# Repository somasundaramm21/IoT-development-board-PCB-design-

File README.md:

# IoT-development-board-PCB-design-
PCB Design and Kicad files for IoT development board

# 🔧 ESP32-C3 IoT Development Board – Designed with KiCad 8

This repository showcases the complete design journey of a **medium-complexity, four-layer IoT development board**, created using **KiCad 8**. The board features the **ESP32-C3** microcontroller along with built-in **environmental sensors**, **flash memory**, **microSD card support**, and a robust **power management system**—making it a powerful and flexible platform for modern IoT applications.

Unlike previous KiCad projects where I only explored new features, this time I set out to **test KiCad 8 in a real-world design workflow**—from schematic to layout, all the way to manufacturing and hardware validation. The result is this versatile, fully functional development board, designed, tested, and optimized using KiCad 8's latest capabilities.

---

## ✨ Key Features

- ✅ Real-world hardware tested with iterative debugging
- 🛠️ Designed entirely in **KiCad 8**
- ⚡️ Powered by **ESP32-C3** (RISC-V + Wi-Fi + BLE)
- 🔋 Battery and USB-C powered with onboard charging circuit
- 📦 Includes **SPI flash** and **microSD card** for flexible data storage
- 🌡️ Built-in sensors for real-time environmental monitoring
- 🧠 Expandable with AI/LLM capabilities using OpenAI-ESP32

---

## 📐 Tech Specs

### 🧠 Core Components

- **Microcontroller**: ESP32-C3 (RISC-V, Wi-Fi 4, Bluetooth Low Energy)
- **Power Input**: USB-C (for power and data) or LiPo battery (via JST)
- **Power Management**:
  - Dedicated LiPo charging circuit
  - Onboard 3.3V and 5V voltage regulators
- **Storage**:
  - MicroSD card slot for local logging
  - External SPI Flash for config/firmware/data

### 🌡️ Sensors & Inputs

- **BME280**: Temperature, humidity, and pressure
- **Ambient Light Sensor**
- **Microphone with Pre-Amplifier**: Sound monitoring and audio input

### 🔌 Interfaces

- **Protocols**: I2C, SPI
- **USB-to-UART Bridge**: For easy programming and serial debugging
- **GPIO Header**: Expandable for external devices/sensors
- **Test Points**: Available for hardware probing and diagnostics

### 🎛️ User Interaction

- **Buttons**: Boot and Reset
- **Indicators**: Status LEDs for power, charge, and operation
- **Form Factor**:
  - 4-layer PCB (signal, power, and ground planes)
  - Compact and EMI-conscious layout
  - Designed for manufacturability and hand-assembly

---

## 🌍 Applications

This board is a multipurpose platform designed for both prototyping and deployment in:

### 📊 Environmental Monitoring
Use the BME280 and light sensor to build smart weather stations, monitor air quality, or automate greenhouse conditions.

### 🧪 Data Logging
With both SPI flash and SD card, this board is perfect for remote or mobile data logging applications like field research or industrial monitoring.

### 🔋 Battery-Powered IoT Devices
Efficient power management and LiPo support allow you to create portable IoT nodes, wearables, or smart agriculture tools.

### 🔊 Audio-Responsive Systems
Use the microphone + preamp setup for audio monitoring, voice triggers, or sound-based analytics.

---

## 🤖 AI Integration with OpenAI-ESP32

This board is not just for sensors and data—it's also designed for **edge AI experiments**.

With the **OpenAI-ESP32 Arduino library** provided by Espressif, your IoT board can now:

- 🔈 **Understand Voice Commands**  
  Use the onboard microphone to build a smart home assistant that reacts to your natural language.

- 📈 **Analyze Sensor Trends**  
  Combine sensor data with OpenAI’s LLMs to generate meaningful summaries, alerts, or insights.

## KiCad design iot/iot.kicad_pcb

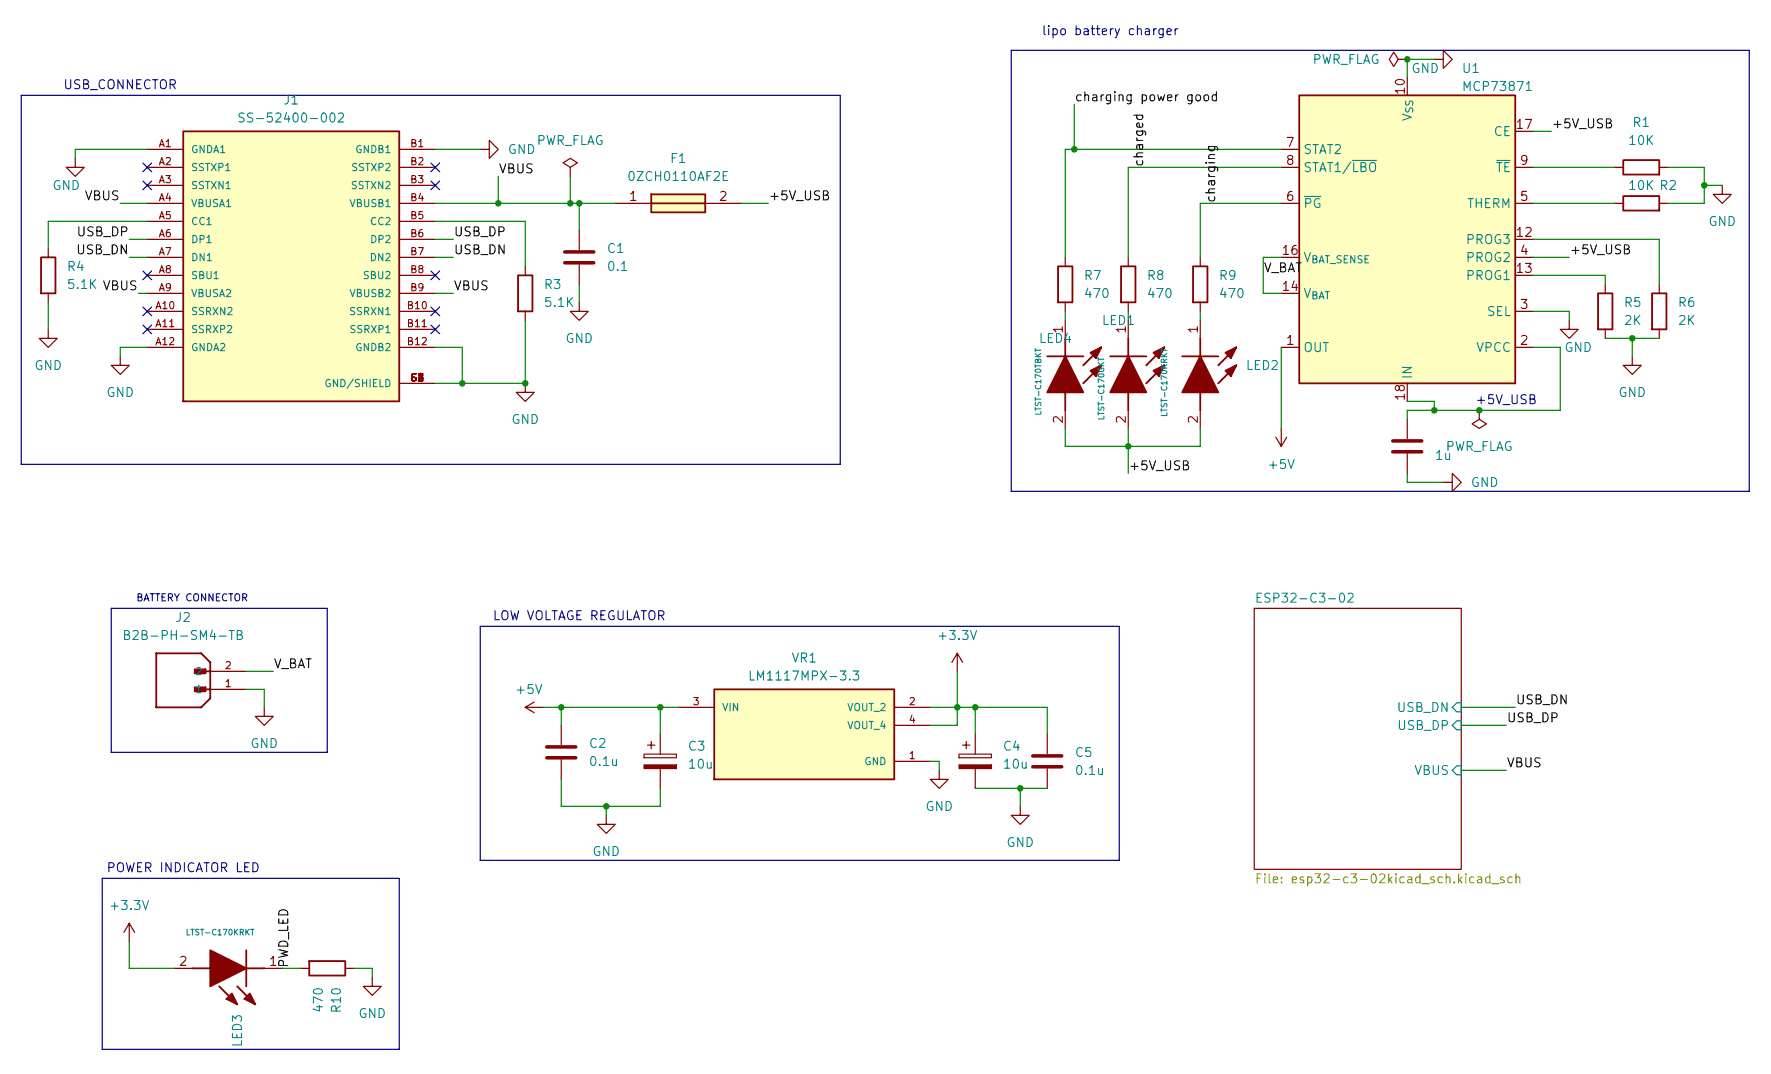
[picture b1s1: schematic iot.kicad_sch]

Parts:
C1: 0.1; C_0805_2012Metric
C2, C5: 0.1u; C_0805_2012Metric
C3, C4: 10u; RESC3216X125N
C6: 1u; C_0805_2012Metric
F1: 0ZCH0110AF2E; FUSC3226X100N; Manufacturer_Part_Number 0ZCH0110AF2E
J1: SS-52400-002; BELFUSE_SS-52400-002; PARTREV A0
J2: B2B-PH-SM4-TB; JST_B2B-PH-SM4-TB; PARTREV N/A
LED1: LTST-C170GKT; LEDC2012X120N; Manufacturer_Part_Number LTST-C170GKT; Mouser Part Number 859-LTST-C170GKT
LED2, LED3: LTST-C170KRKT; LEDC2012X120N; Manufacturer_Part_Number LTST-C170KRKT; Mouser Part Number 859-LTST-C170KRKT
LED4: LTST-C170TBKT; LEDC2012X120N; Manufacturer_Part_Number LTST-C170TBKT; Mouser Part Number 859-LTST-C170TBKT
R1, R2: 10K; R_0805_2012Metric
R3, R4: 5.1K; R_0805_2012Metric
R5, R6: 2K; R_0805_2012Metric
R7, R8, R9, R10: 470; R_0805_2012Metric
U1: MCP73871; QFN-20-1EP_4x4mm_P0.5mm_EP2.5x2.5mm
VR1: LM1117MPX-3.3; VREG_LM1117MPX-3.3; PARTREV O

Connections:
+3.3V: C4.1, C5.1, LED3.2 (A), VR1.2 (VOUT_2), VR1.4 (VOUT_4); also elsewhere on the board
+5V: C2.1, C3.1, U1.1 (OUT), U1.20 (OUT), VR1.3 (VIN)
/PWD_LED: LED3.1 (K), R10.2
/USB_DN: J1.A7 (DN1), J1.B7 (DN2); also elsewhere on the board
/USB_DP: J1.A6 (DP1), J1.B6 (DP2); also elsewhere on the board
/VBUS: C1.1, F1.1, J1.A4 (VBUSA1), J1.A9 (VBUSA2), J1.B4 (VBUSB1), J1.B9 (VBUSB2); also elsewhere on the board
/V_BAT: J2.2, U1.14 (V_{BAT}), U1.15 (V_{BAT}), U1.16 (V_{BAT_SENSE})
/charged: R8.1, U1.8 (STAT1/~LBO)
/charging: R9.1, U1.6 (~PG)
/charging power good: R7.1, U1.7 (STAT2)
GND: C1.2, C2.2, C3.2, C4.2, C5.2, C6.2, J1.A1 (GNDA1), J1.A12 (GNDA2), J1.B1 (GNDB1), J1.B12 (GNDB2), J1.G1 (GND/SHIELD), J1.G2 (GND/SHIELD), J1.G3 (GND/SHIELD), J1.G4 (GND/SHIELD), J1.S1 (GND/SHIELD), J1.S2 (GND/SHIELD), J1.S3 (GND/SHIELD), J1.S4 (GND/SHIELD), J2.1, R1.2, R2.2, R3.2, R4.2, R5.2, R6.2, R10.1, U1.3 (SEL), U1.10 (V_{SS}), U1.11 (V_{SS}), U1.21 (V_{SS}), VR1.1 (GND); also elsewhere on the board
unnamed: J1.A5 (CC1), R4.1
unnamed: J1.B5 (CC2), R3.1
unnamed: LED1.1 (K), R8.2
unnamed: LED2.1 (K), R9.2
unnamed: LED4.1 (K), R7.2
unnamed: R5.1, U1.13 (PROG1)
unnamed: R6.1, U1.12 (PROG3)
unnamed: R2.1, U1.5 (THERM)
unnamed: R1.1, U1.9 (~TE)

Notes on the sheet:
lipo battery charger
POWER INDICATOR LED
+5V_USB
USB_CONNECTOR
LOW VOLTAGE REGULATOR
BATTERY CONNECTOR

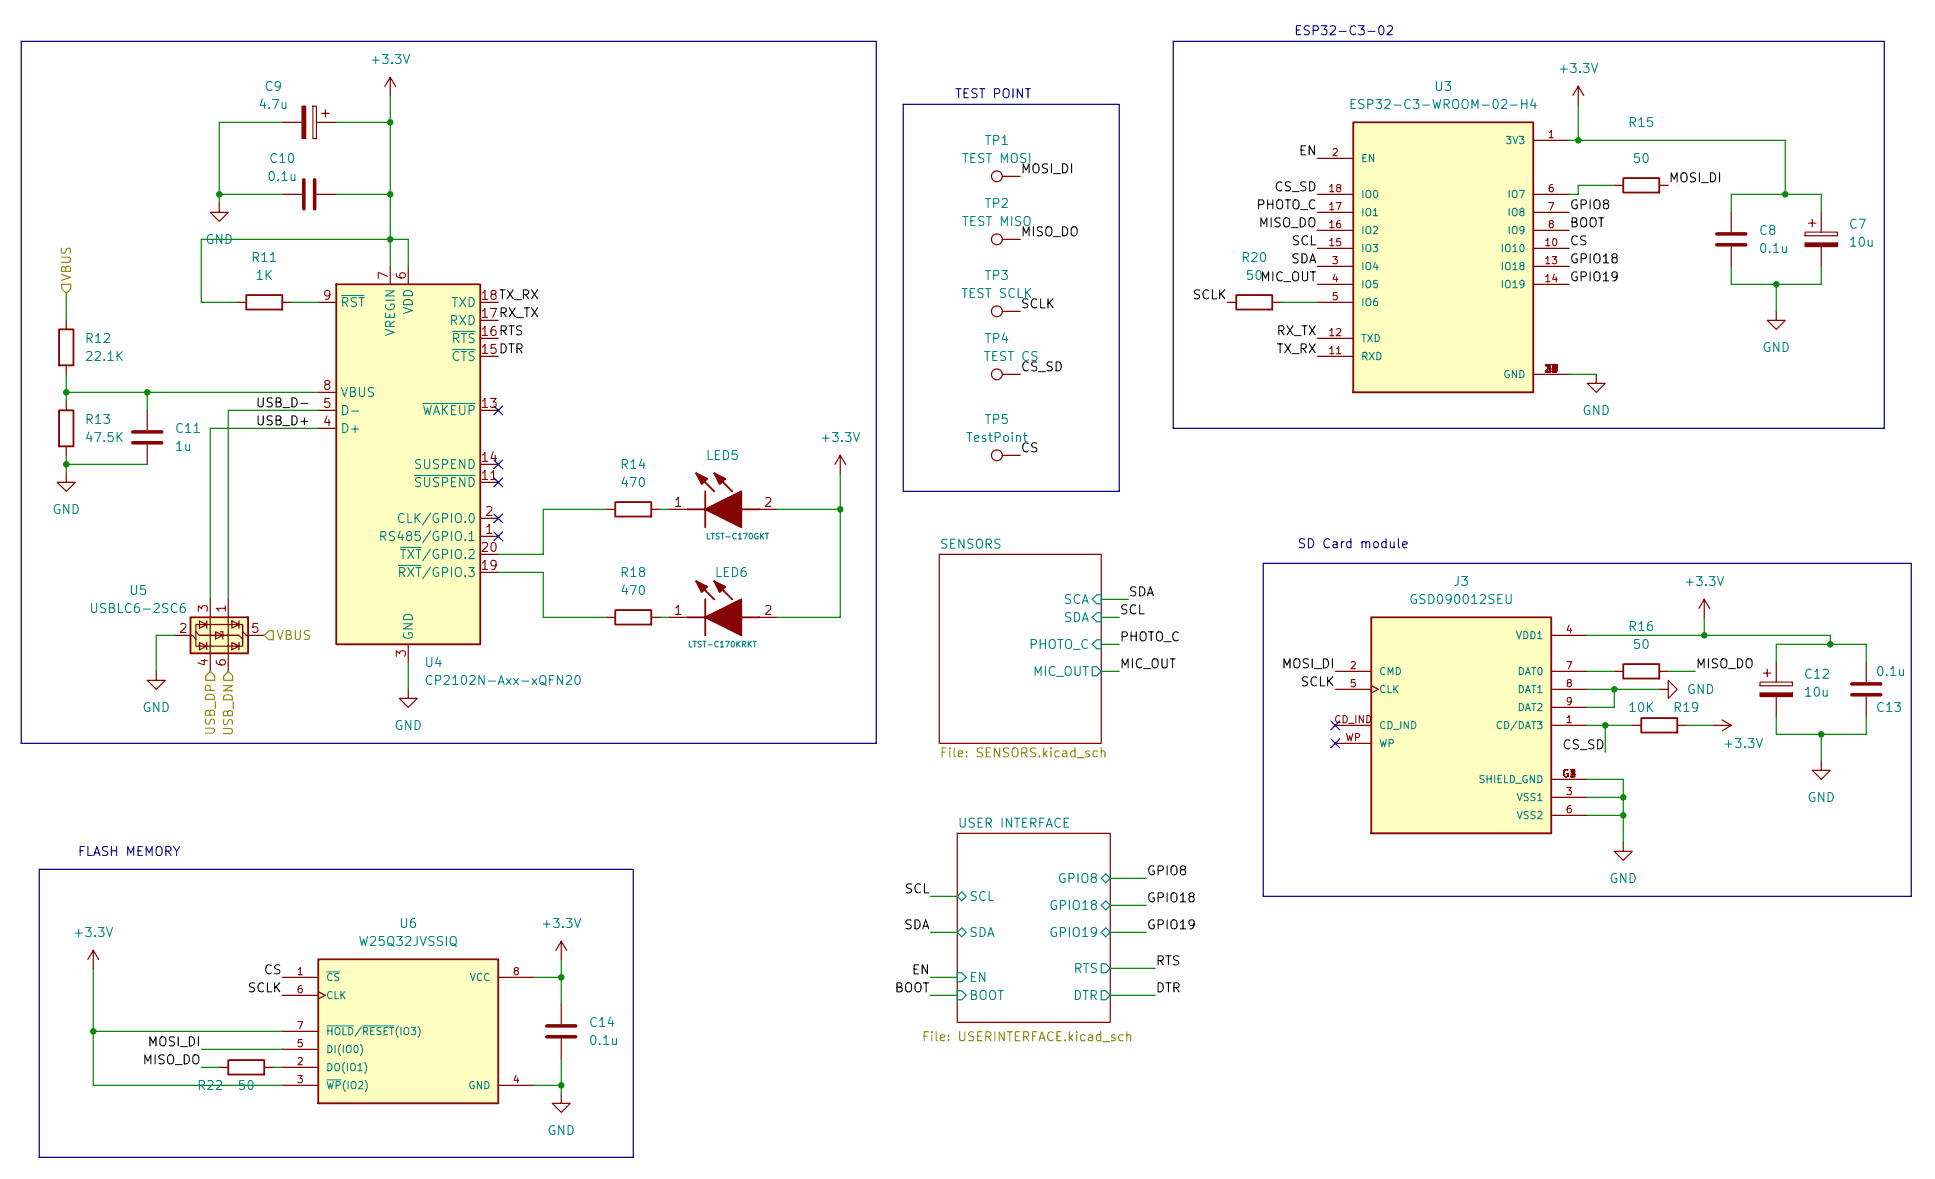
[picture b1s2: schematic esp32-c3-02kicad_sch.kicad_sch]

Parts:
C7, C12: 10u; RESC3216X125N
C8, C10, C13, C14: 0.1u; C_0805_2012Metric
C9: 4.7u; RESC3216X125N
C11: 1u; C_0805_2012Metric
J3: GSD090012SEU; AMPHENOL_GSD090012SEU; PARTREV E
LED5: LTST-C170GKT; LEDC2012X120N; Manufacturer_Part_Number LTST-C170GKT; Mouser Part Number 859-LTST-C170GKT
LED6: LTST-C170KRKT; LEDC2012X120N; Manufacturer_Part_Number LTST-C170KRKT; Mouser Part Number 859-LTST-C170KRKT
R11: 1K; R_0805_2012Metric
R12: 22.1K; R_0805_2012Metric
R13: 47.5K; R_0805_2012Metric
R14, R18: 470; R_0805_2012Metric
R15, R16, R20, R22: 50; R_0805_2012Metric
R19: 10K; R_0805_2012Metric
TP1: TEST MOSI; TestPoint_Pad_D1.0mm
TP2: TEST MISO; TestPoint_Pad_D1.0mm
TP3: TEST SCLK; TestPoint_Pad_D1.0mm
TP4: TEST CS; TestPoint_Pad_D1.0mm
TP5: TestPoint; TestPoint_Pad_D1.0mm
U3: ESP32-C3-WROOM-02-H4; MODULE_ESP32-C3-WROOM-02-H4; DigiKey_Part_Number 1965-ESP32-C3-WROOM-02-H4CT-ND
U4: CP2102N-Axx-xQFN20; IC_CP2102N-A01-GQFN20
U5: USBLC6-2SC6; SOT-23-6
U6: W25Q32JVSSIQ; SOIC127P790X216-8N; M_PART_NUMBER W25QXX

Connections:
+3.3V: C7.1, C8.1, C9.1, C10.2, C12.1, C13.1, C14.1, J3.4 (VDD1), LED5.2 (A), LED6.2 (A), R11.1, R19.2, U3.1 (3V3), U4.6 (VDD), U4.7 (VREGIN), U6.3 (~WP(IO2)), U6.7 (~HOLD/~RESET(IO3)), U6.8 (VCC); also elsewhere on the board
/ESP32-C3-02/BOOT: U3.8 (IO9); also elsewhere on the board
/ESP32-C3-02/CS: TP5.1, U3.10 (IO10), U6.1 (~CS)
/ESP32-C3-02/CS_SD: J3.1 (CD/DAT3), R19.1, TP4.1, U3.18 (IO0)
/ESP32-C3-02/DTR: U4.15 (~CTS); also elsewhere on the board
/ESP32-C3-02/EN: U3.2 (EN); also elsewhere on the board
/ESP32-C3-02/GPIO8: U3.7 (IO8); also elsewhere on the board
/ESP32-C3-02/GPIO18: U3.13 (IO18); also elsewhere on the board
/ESP32-C3-02/GPIO19: U3.14 (IO19); also elsewhere on the board
/ESP32-C3-02/MIC_OUT: U3.4 (IO5); also elsewhere on the board
/ESP32-C3-02/MISO_DO: R16.2, R22.1, TP2.1, U3.16 (IO2)
/ESP32-C3-02/MOSI_DI: J3.2 (CMD), R15.2, TP1.1, U6.5 (DI(IO0))
/ESP32-C3-02/PHOTO_C: U3.17 (IO1); also elsewhere on the board
/ESP32-C3-02/RTS: U4.16 (~RTS); also elsewhere on the board
/ESP32-C3-02/RX_TX: U3.12 (TXD), U4.17 (RXD)
/ESP32-C3-02/SCL: U3.15 (IO3); also elsewhere on the board
/ESP32-C3-02/SCLK: J3.5 (CLK), R20.1, TP3.1, U6.6 (CLK)
/ESP32-C3-02/SDA: U3.3 (IO4); also elsewhere on the board
/ESP32-C3-02/TX_RX: U3.11 (RXD), U4.18 (TXD)
/ESP32-C3-02/USB_D+: U4.4 (D+), U5.3 (I/O2)
/ESP32-C3-02/USB_D-: U4.5 (D-), U5.1 (I/O1)
/USB_DN: U5.6 (I/O1); also elsewhere on the board
/USB_DP: U5.4 (I/O2); also elsewhere on the board
/VBUS: R12.1, U5.5 (VBUS); also elsewhere on the board
GND: C7.2, C8.2, C9.2, C10.1, C11.2, C12.2, C13.2, C14.2, J3.3 (VSS1), J3.6 (VSS2), J3.8 (DAT1), J3.9 (DAT2), J3.G1 (SHIELD_GND), J3.G2 (SHIELD_GND), J3.G3 (SHIELD_GND), J3.G4 (SHIELD_GND), R13.2, U3.9 (GND), U3.19 (GND), U3.20 (GND), U3.21 (GND), U3.22 (GND), U3.23 (GND), U3.24 (GND), U3.25 (GND), U3.26 (GND), U3.27 (GND), U3.28 (GND), U3.29 (GND), U3.30 (GND), U3.31 (GND), U3.32 (GND), U3.33 (GND), U3.34 (GND), U3.35 (GND), U3.36 (GND), U3.37 (GND), U3.38 (GND), U3.39 (GND), U4.3 (GND), U4.12 (GND), U4.21 (GND), U5.2 (GND), U6.4 (GND); also elsewhere on the board
unnamed: J3.7 (DAT0), R16.1
unnamed: LED5.1 (K), R14.2
unnamed: LED6.1 (K), R18.2
unnamed: R20.2, U3.5 (IO6)
unnamed: R15.1, U3.6 (IO7)
unnamed: C11.1, R12.2, R13.1, U4.8 (VBUS)
unnamed: R11.2, U4.9 (~RST)
unnamed: R18.1, U4.19 (~RXT/GPIO.3)
unnamed: R14.1, U4.20 (~TXT/GPIO.2)
unnamed: R22.2, U6.2 (DO(IO1))

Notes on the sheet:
TEST POINT
ESP32-C3-02
FLASH MEMORY
SD Card module

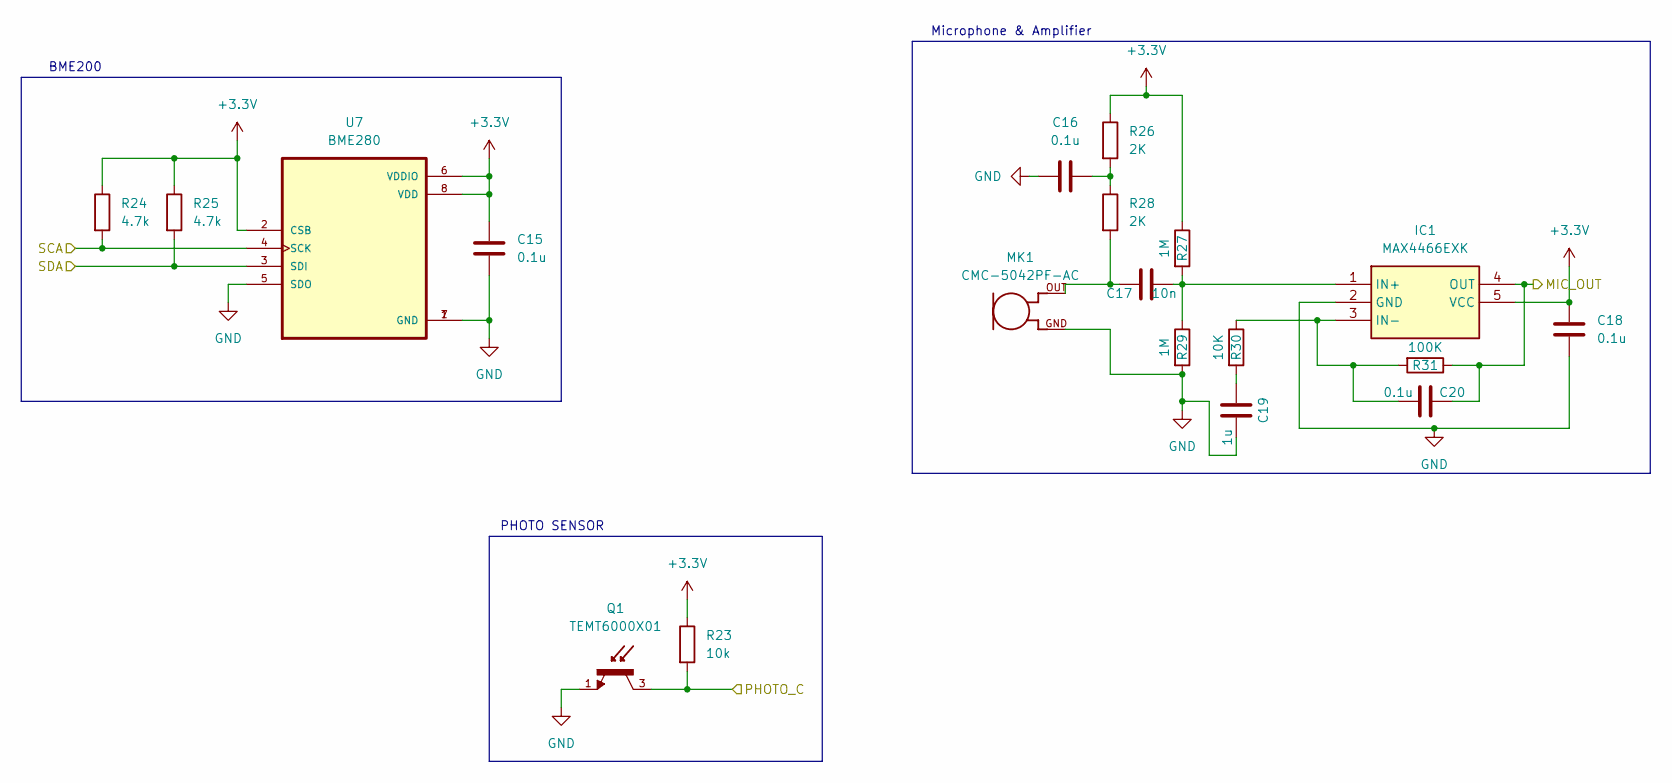
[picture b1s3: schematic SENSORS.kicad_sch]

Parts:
C15, C16, C18, C20: 0.1u; C_0805_2012Metric
C17: 10n; C_0805_2012Metric
C19: 1u; C_0805_2012Metric
IC1: MAX4466EXK; SOT65P210X110-5N; Manufacturer_Part_Number MAX4466EXK; Mouser Part Number N/A
MK1: CMC-5042PF-AC; CUI_CMC-5042PF-AC
Q1: TEMT6000X01; TRANS_TEMT6000X01; PARTREV 1.9
R23: 10k; R_0805_2012Metric
R24, R25: 4.7k; R_0805_2012Metric
R26, R28: 2K; R_0805_2012Metric
R27, R29: 1M; R_0805_2012Metric
R30: 10K; R_0805_2012Metric
R31: 100K; R_0805_2012Metric
U7: BME280; PSON65P250X250X100-8N

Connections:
+3.3V: C15.1, C18.1, IC1.5 (VCC), R23.1, R24.1, R25.1, R26.1, R27.1, U7.2 (CSB), U7.6 (VDDIO), U7.8 (VDD); also elsewhere on the board
/ESP32-C3-02/MIC_OUT: C20.2, IC1.4 (OUT), R31.1; also elsewhere on the board
/ESP32-C3-02/PHOTO_C: Q1.3, R23.2; also elsewhere on the board
/ESP32-C3-02/SCL: R25.2, U7.3 (SDI); also elsewhere on the board
/ESP32-C3-02/SDA: R24.2, U7.4 (SCK); also elsewhere on the board
GND: C15.2, C16.1, C18.2, C19.1, IC1.2 (GND), MK1.GND, Q1.1, R29.2, U7.1 (GND), U7.5 (SDO), U7.7 (GND); also elsewhere on the board
unnamed: C16.2, R26.2, R28.1
unnamed: C17.2, MK1.OUT, R28.2
unnamed: C19.2, R30.2
unnamed 34: C17.1, IC1.1 (IN+), R27.2, R29.1; also elsewhere on the board
unnamed 35: C20.1, IC1.3 (IN-), R30.1, R31.2; also elsewhere on the board

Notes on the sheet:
PHOTO SENSOR
Microphone & Amplifier
BME200

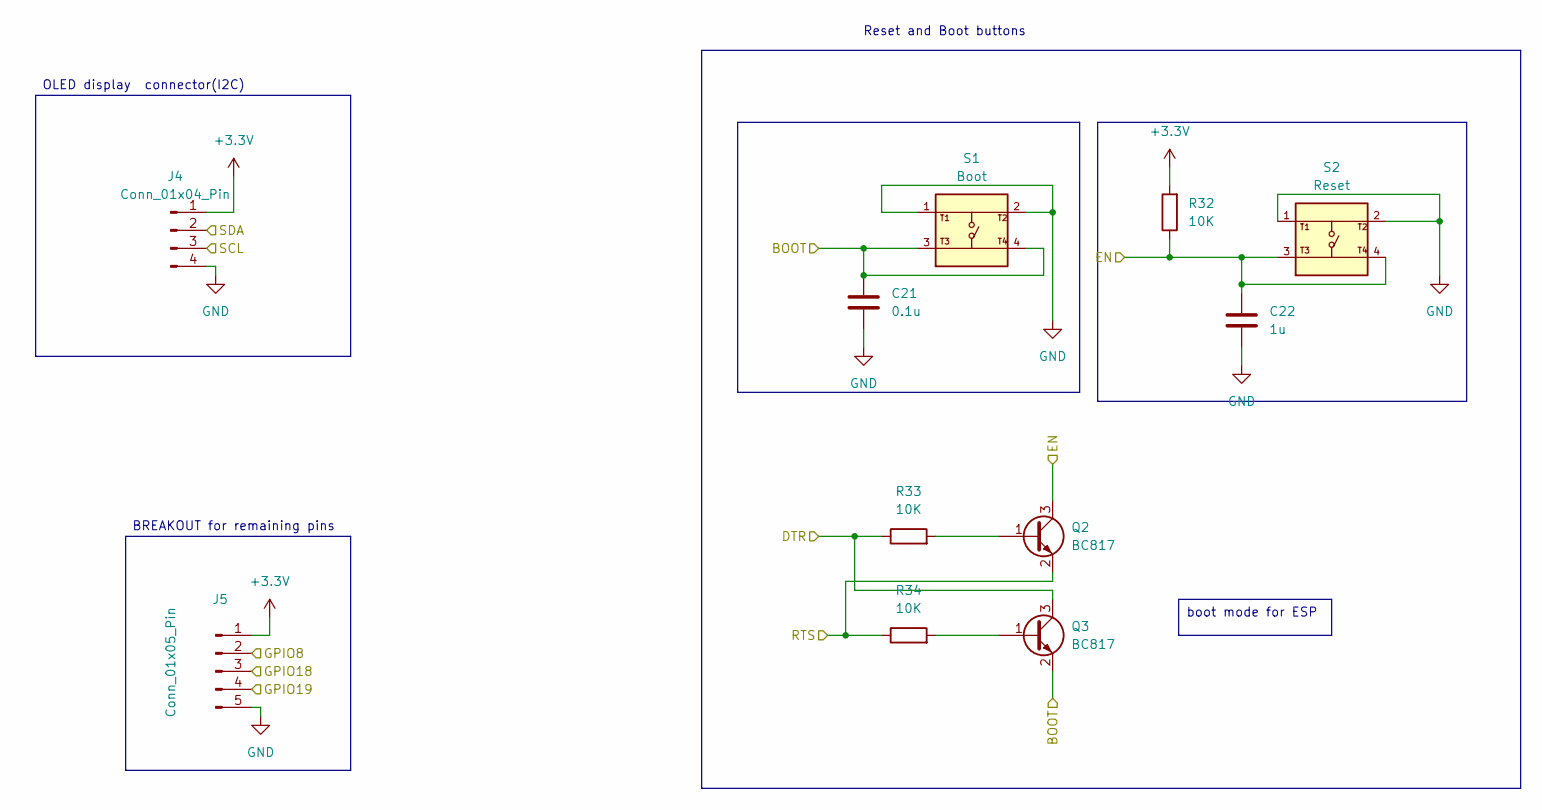
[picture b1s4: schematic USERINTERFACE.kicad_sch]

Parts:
C21: 0.1u; C_0805_2012Metric
C22: 1u; C_0805_2012Metric
J4: Conn_01x04_Pin; PinHeader_1x04_P2.54mm_Vertical
J5: Conn_01x05_Pin; PinHeader_1x05_P2.54mm_Vertical
Q2, Q3: BC817; SOT-23
R32, R33, R34: 10K; R_0805_2012Metric
S1: Boot; SW_USLPT2819DT2TR; PARTREV P
S2: Reset; SW_USLPT2819DT2TR; PARTREV P

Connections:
+3.3V: J4.1, J5.1, R32.2; also elsewhere on the board
/ESP32-C3-02/BOOT: C21.1, Q3.2 (E), S1.3, S1.4; also elsewhere on the board
/ESP32-C3-02/DTR: Q3.3 (C), R33.1; also elsewhere on the board
/ESP32-C3-02/EN: C22.1, Q2.3 (C), R32.1, S2.3, S2.4; also elsewhere on the board
/ESP32-C3-02/GPIO8: J5.2; also elsewhere on the board
/ESP32-C3-02/GPIO18: J5.3; also elsewhere on the board
/ESP32-C3-02/GPIO19: J5.4; also elsewhere on the board
/ESP32-C3-02/RTS: Q2.2 (E), R34.1; also elsewhere on the board
/ESP32-C3-02/SCL: J4.3; also elsewhere on the board
/ESP32-C3-02/SDA: J4.2; also elsewhere on the board
GND: C21.2, C22.2, J4.4, J5.5, S1.1, S1.2, S2.1, S2.2; also elsewhere on the board
unnamed: Q2.1 (B), R33.2
unnamed: Q3.1 (B), R34.2

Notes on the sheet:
boot mode for ESP
OLED display connector(I2C)
Reset and Boot buttons
BREAKOUT for remaining pins

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
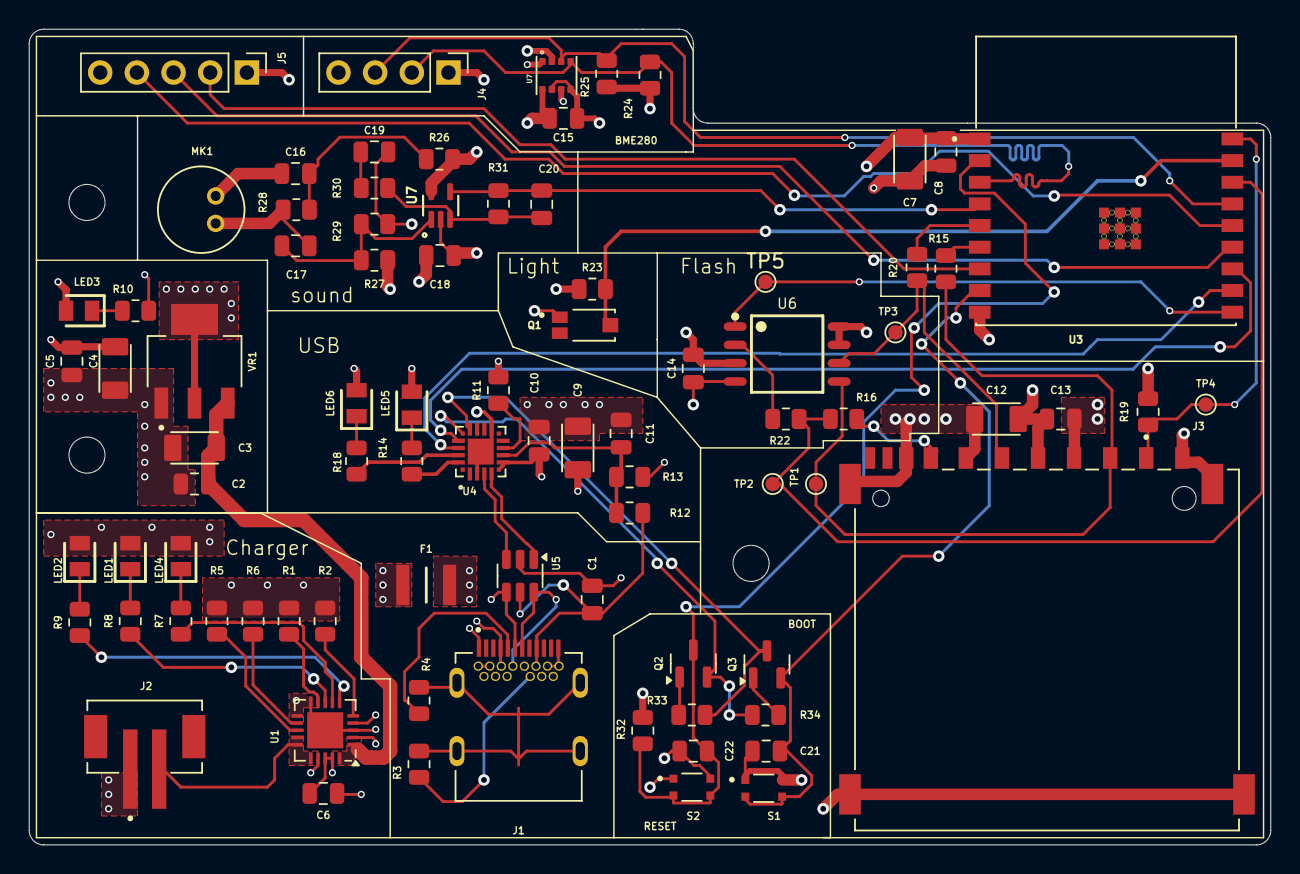
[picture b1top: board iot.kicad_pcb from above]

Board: 4 copper layers, 86.0 x 56.5 mm, 85 parts (0 on the bottom side), 58 nets.

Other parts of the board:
U7#2: MAX4466EXK; SOT65P210X110-5N

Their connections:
+3.3V: U7#2.5 (VCC); also elsewhere on the board
/ESP32-C3-02/MIC_OUT: U7#2.4 (OUT); also elsewhere on the board
GND: U7#2.2 (GND); also elsewhere on the board
unnamed 34: U7#2.1 (IN+); also elsewhere on the board
unnamed 35: U7#2.3 (IN-); also elsewhere on the board
